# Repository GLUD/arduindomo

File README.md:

arduindomo
==========

El objetivo del proyecto es integrar a la comunidad universitaria por medio del el uso de tecnologías libres fomentando  su filosofía , principios y  ventajas que tiene el hardware libre respecto al hardware propietario y sus aplicaciones en domótica  sobre un ambiente web , el proyecto buscar ir fortaleciendo las practicas de programación de microcontroladores y el uso de aplicaciones  sobre el modelo de internet TCP/IP en ambientes GNU Linux y sin el requisito de tener sólidos conocimientos en electrónica , de hecho es un proyecto que busca romper la brecha digital entre distintas áreas de ingenieria , artes y cultura. Aquellas personas  con conocimientos en electrónica puede llegar a integrar software de simulación , emulación , esquemáticos (PCB) y con la documentación accesible al público.

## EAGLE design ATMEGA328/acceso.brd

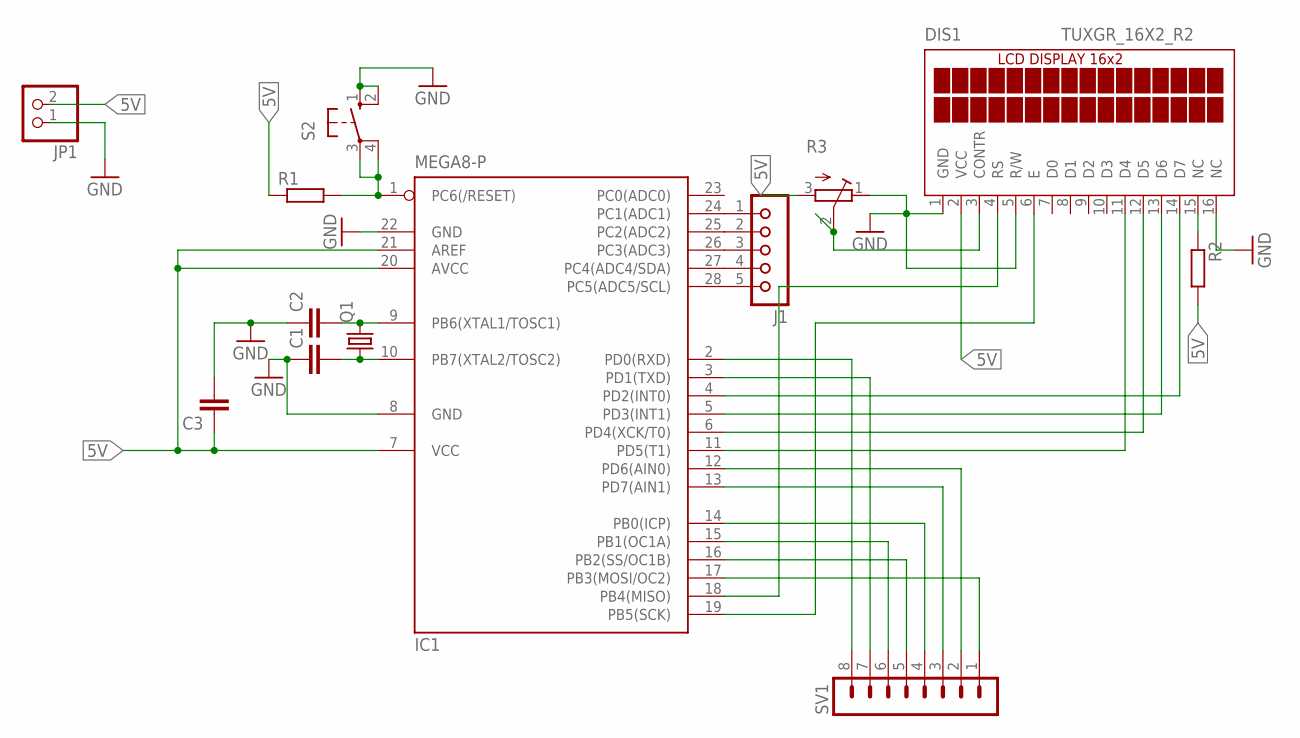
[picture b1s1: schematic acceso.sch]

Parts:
C1, C2, C3: C2,5-3; C2.5-3
DIS1: TUXGR_16X2_R2
IC1: MEGA8-P; DIL28-3
J1: JU05
JP1: PINHD-1X2; 1X02
Q1: CRYSTALTC26V; TC26V
R1, R2: R-EU_0204/5; 0204/5
R3: R-TRIMM43P; RTRIM43P
S2: 10-XX; B3F-10XX
SV1: MA08-1

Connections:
5V: C3.1, DIS1.2 (VCC), IC1.7 (VCC), IC1.20 (AVCC), IC1.21 (AREF), JP1.2, R1.1, R2.2, R3.3 (A)
GND: C1.1, C2.1, C3.2, DIS1.1 (GND), DIS1.5 (R/W), DIS1.16 (NC), IC1.8 (GND), IC1.22 (GND), JP1.1, R3.1 (E), S2.1 (S), S2.2 (S1)
unnamed: IC1.2 (PD0(RXD)), SV1.8
unnamed: IC1.3 (PD1(TXD)), SV1.7
unnamed: IC1.15 (PB1(OC1A)), SV1.6
unnamed: IC1.16 (PB2(SS/OC1B)), SV1.5
unnamed: IC1.14 (PB0(ICP)), SV1.4
unnamed: IC1.13 (PD7(AIN1)), SV1.3
unnamed: IC1.12 (PD6(AIN0)), SV1.2
unnamed: DIS1.4 (RS), IC1.18 (PB4(MISO))
unnamed: DIS1.6 (E), IC1.19 (PB5(SCK))
unnamed: DIS1.11 (D4), IC1.11 (PD5(T1))
unnamed: DIS1.12 (D5), IC1.6 (PD4(XCK/T0))
unnamed: DIS1.13 (D6), IC1.5 (PD3(INT1))
unnamed: DIS1.15 (NC), R2.1
unnamed: C2.2, IC1.9 (PB6(XTAL1/TOSC1)), Q1.2
unnamed: C1.2, IC1.10 (PB7(XTAL2/TOSC2)), Q1.1
unnamed: IC1.1 (PC6(/RESET)), R1.2, S2.3, S2.4 (P1)
unnamed: IC1.17 (PB3(MOSI/OC2)), SV1.1
unnamed: DIS1.14 (D7), IC1.4 (PD2(INT0))
unnamed: IC1.24 (PC1(ADC1)), J1.1
unnamed: IC1.25 (PC2(ADC2)), J1.2
unnamed: DIS1.3 (CONTR), R3.2 (S)
unnamed: IC1.26 (PC3(ADC3)), J1.3
unnamed: IC1.27 (PC4(ADC4/SDA)), J1.4
unnamed: IC1.28 (PC5(ADC5/SCL)), J1.5

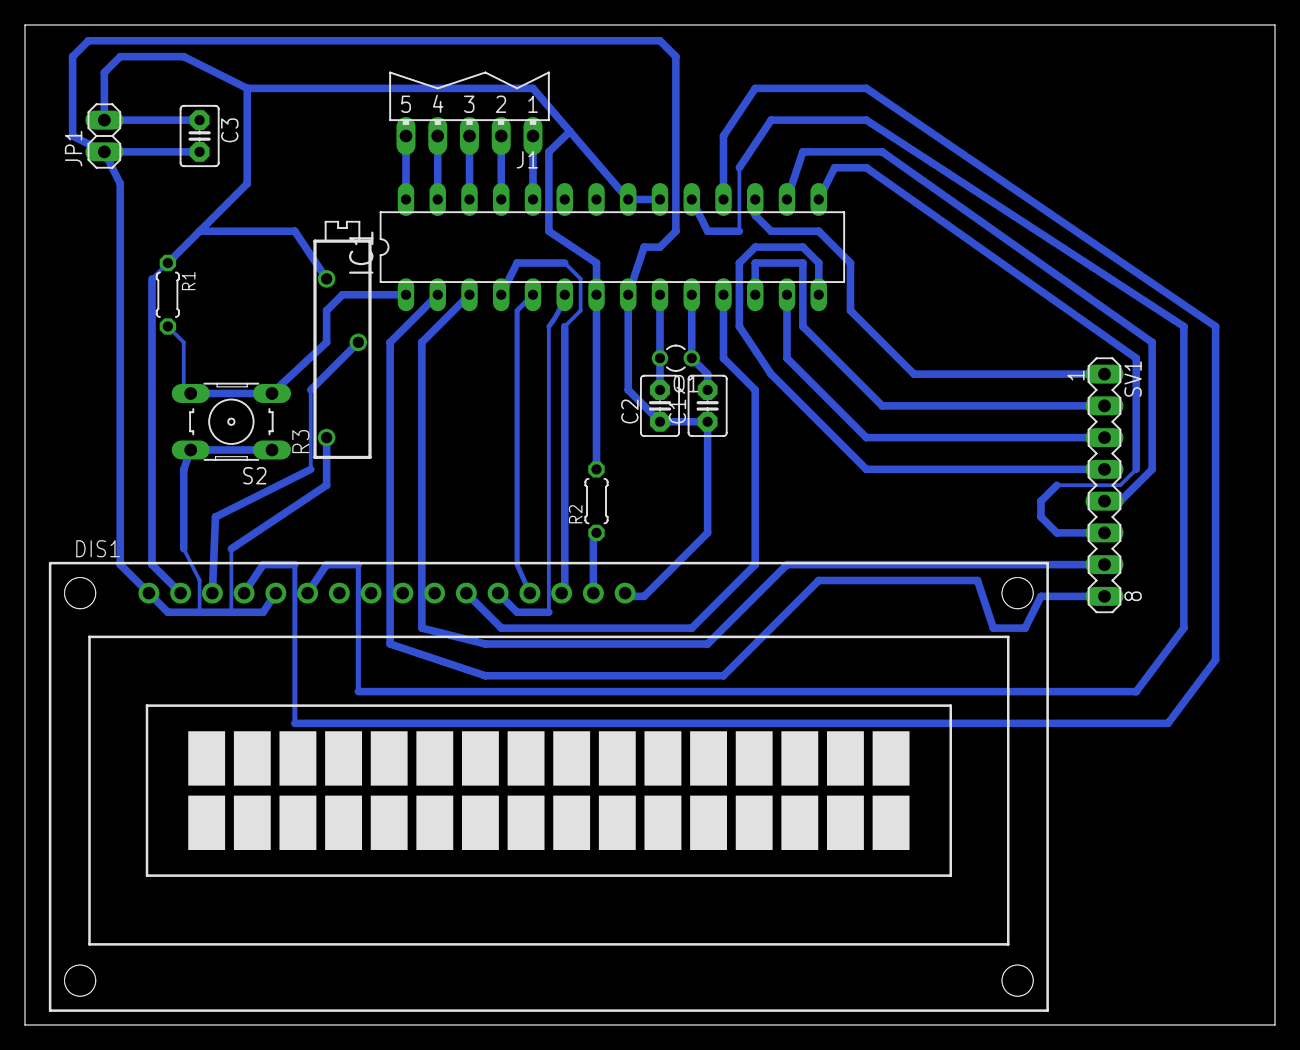
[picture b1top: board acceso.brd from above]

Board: 2 copper layers, 100.0 x 80.0 mm, 13 parts (0 on the bottom side), 26 nets.

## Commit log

2014-11-11 [doc] se hace una replica del soberania alimentaria en el glud
